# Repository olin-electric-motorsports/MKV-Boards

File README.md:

# MKV-Boards
Repository for all OEM MKV PCB Projects

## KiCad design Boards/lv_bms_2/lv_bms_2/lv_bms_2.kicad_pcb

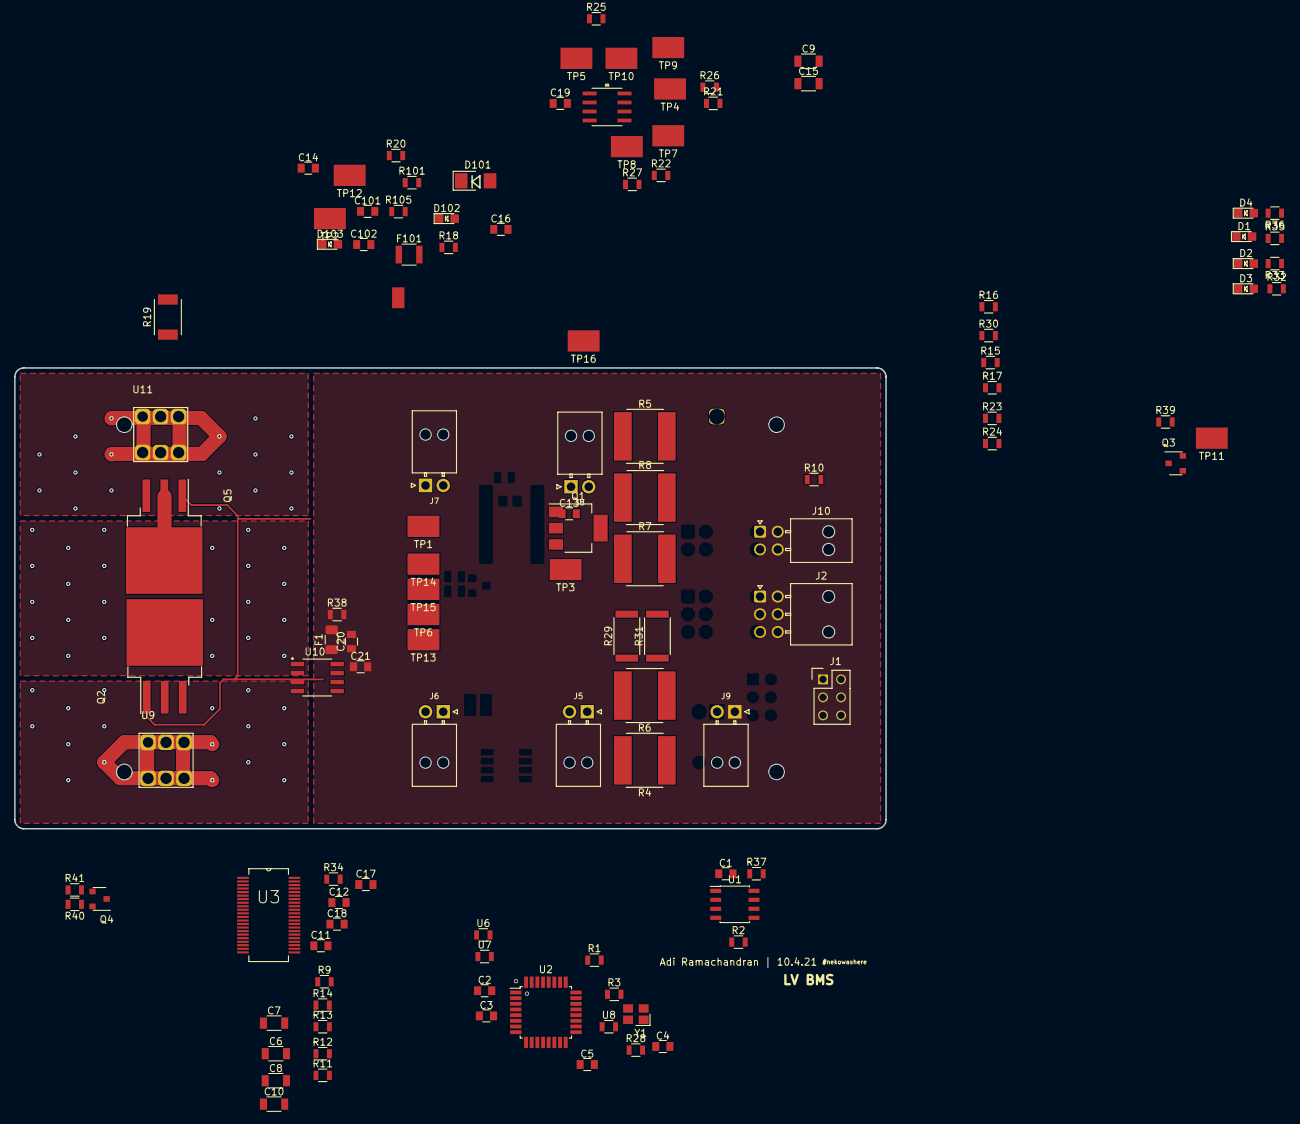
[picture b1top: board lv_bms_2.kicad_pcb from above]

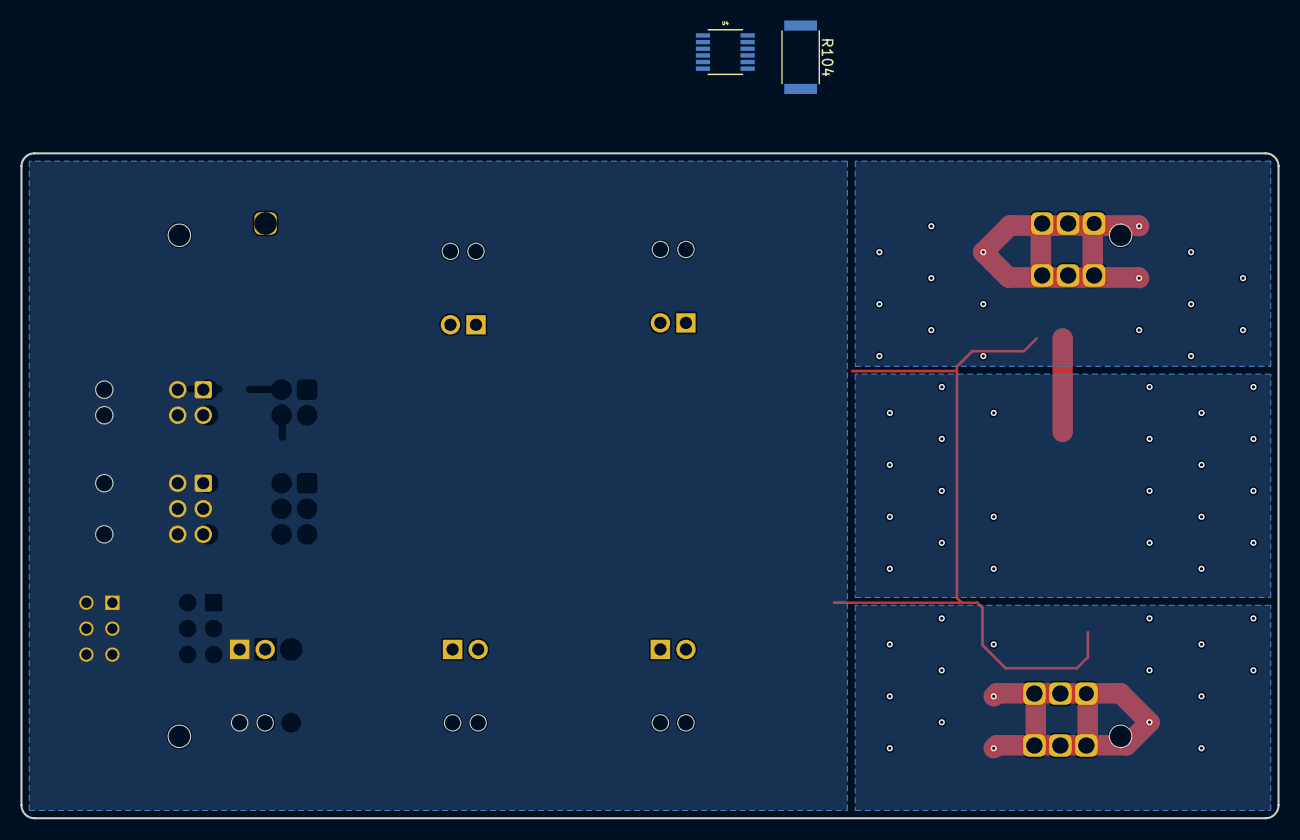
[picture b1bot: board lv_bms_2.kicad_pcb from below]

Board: 4 copper layers, 122.9 x 65.0 mm, 117 parts (2 on the bottom side), 76 nets.

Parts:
C1, C2, C13, C18, C19, C101: C_0.1uF; C_0805_OEM
C3: C_100pF; C_0805_OEM
C4, C5: C_30pF; C_0805_OEM
C6, C7, C8, C9, C10, C15: C_10nF; C_1206_OEM
C11, C12, C17, C21: C_1uF; C_0805_OEM
C14: C_470pF; C_0805_OEM
C16: C_10uF; C_0805_OEM
C20: C_1nf; C_0805_OEM
C102: C_2.2uF; C_0805_OEM
D1, D2: LED_0805_Red; LED_0805_OEM
D3, D4, D102, D103: LED_0805; LED_0805_OEM
D101: D_Zener_18V; DO-214AA
F1: 0685P9500-01; Fuse_1206
F101: F_500mA_16V; Fuse_1210
J1: CONN_02X03; Pin_Header_Straight_2x03
J2: NanoFit_RA_TH_06; NanoFit_RA_6
J5, J6, J7, J8, J9: NanoFit_RA_TH_02; NanoFit_Molex_1x02x2.50mm_Angled_OEM
J10: NanoFit_RA_TH_04; NanoFit_RA_4
Q1: NSS1C201MZ4; SOT-223
Q2, Q5: SQM110P06; TO-263-3-TabPin2
Q3, Q4: MMBF170; SOT-23-3_OEM
R1, R9, R10, R11, R12, R13, R14: R_100; R_0805_OEM
R2: R_120_DNP; R_0805_OEM
R3, R15, R16, R17, R20, R23, R24, R28, R30, R34, R40: R_10K; R_0805_OEM
R4, R5, R6, R7, R8: R_30_6W_1%; 356030RFT
R18, R21, R26, R37, R38, R39: R_100K; R_0805_OEM
R19: R_1.5k; R_2010_Vishay
R22, R27: R_1M; R_0805_OEM
R25: R_402K; R_0805_OEM
R29, R31, R104: R_0_2512; R_2512_OEM
R32, R33, R35, R36, R105: R_200; R_0805_OEM
R41: R_10; R_0805_OEM
R101: R_1K; R_0805_OEM
TP1, TP2, TP3, TP4, TP5, TP6, TP7, TP8, TP9, TP10, TP11, TP12, TP13, TP14, TP15, TP16: Test_Point_SMD
U1: MCP2561-E_SN; SOIC-8_3.9x4.9mm_Pitch1.27mm_OEM
U2: ATMEGA16M1; TQFP-32_7x7mm_Pitch0.8mm
U3: LTC6810HG-2; SOP50P780X200-44N
U4: LT3066IMSE-5; MSOP-12_MSE
U5: LT1017IS8; SO-8_S
U6, U7, U8: R_500; R_0805_OEM
U9, U11: redcube-7461057; redcube_pressfit_6pin
U10: ACHS-7124; OPTO_HCPL-070A-000E
Y1: Crystal_SMD; Crystal_SMD_FA238

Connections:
+5V: C1.1, C2.1, C19.1, C21.1, J1.2, R1.1, R3.1, R15.1, R16.1, R17.1, R23.1, R24.1, R28.1, R30.1, R34.1, R37.1, R104.2, U1.3, U2.4, U5.6, U10.8
/BATTERY_SIDE_DIV_SIG: R21.2, R22.1, TP7.1
/BATT_1: J2.2, R7.2, R12.2
/BATT_2: J2.3, R6.2, R11.2
/BATT_3: J2.4, R5.2, R10.2
/BATT_4: F101.2, J2.5, R4.2, R9.2, R29.2, R31.2, TP12.1, U5.3
/CAN+: J10.4, R2.1, U1.7
/CAN-: J10.3, R2.2, U1.6
/CAN_RX: U1.4, U2.7
/CAN_STBY: R37.2, U1.8, U2.23
/CAN_TX: U1.1, U2.6
/COMP_1_OUT: TP4.1, U2.16, U5.7
/COMP_2_OUT: TP10.1, U2.26, U5.5
/CSB: R28.2, U2.15, U3.36
/CURRENT_SENSE_SIGNAL: U2.28, U10.7
/LED_0_+: R32.1, U2.8
/LED_1_+: R33.1, U2.9
/LED_2_+: R35.1, U2.24
/LOAD_SIDE_CURRENT_PATH: Q5.3, R25.1, R26.1, TP9.1, U11.1
/LOAD_SIDE_DIV_SIG: R26.2, R27.1, TP8.1, U5.4
/LOAD_SWITCH_FET_DRIVE: Q4.1, R38.1, U2.25
/MISO: J1.1, U2.1, U6.1
/MISO_LIM: R34.2, U3.40, U6.2
/MOSI: J1.4, U2.2, U7.1
/MOSI_LIM: U3.41, U7.2
/ON_STATE_CMPNTS_-: C20.2, C21.2, J5.2, J6.2, J7.1, J8.1, J9.1, Q3.3, TP11.1, TP15.1, U10.5
/ON_STATE_CMPNTS_FET_DRIVE: Q3.1, R36.1, R39.1, U2.30
/PACK_SIDE_CURRENT_PATH: F1.2, R21.1, R25.2, TP5.1, U10.1, U10.2
/RESET: J1.5, R3.2, U2.31
/SCK: J1.3, U2.12, U8.1
/SCK_LIM: U3.37, U8.2
/THERM_0_+: J7.2, R30.2, U2.27
/THERM_1_+: J8.2, R24.2, U2.17
/THERM_2_+: J9.2, R23.2, U2.18
/THERM_3_+: J6.1, R17.2, U2.22
/THERM_4_+: J5.1, R16.2, U2.13
/THERM_5_+: R15.2, TP14.1, U2.14
/VREG: C17.1, Q1.3, TP3.1, U3.32
GND: C1.2, C2.2, C3.2, C4.2, C5.2, C11.2, C12.2, C13.2, C14.2, C15.2, C16.2, C17.2, C18.1, C19.2, C101.2, C102.2, D1.1, D2.1, D3.1, D4.1, D101.2, D102.1, D103.1, J1.6, J2.1, J10.1, J10.2, Q3.2, Q4.2, R8.2, R13.2, R20.2, R22.2, R27.2, R38.2, R39.2, TP16.1, U1.2, U2.5, U2.20, U3.1, U3.21, U3.22, U3.23, U3.24, U3.26, U3.27, U3.28, U3.29, U3.34, U3.35, U3.38, U3.39, U3.43, U3.44, U4.6, U4.8, U5.2, Y1.2, Y1.4
unnamed: C3.1, R1.2, U2.19
unnamed: C4.1, U2.11, Y1.1
unnamed: C5.1, U2.10, Y1.3
unnamed: C6.1, R9.1, TP1.1, U3.6, U3.8
unnamed: C6.2, C7.1, R10.1, U3.10
unnamed: C7.2, C8.1, R11.1, U3.12
unnamed: C8.2, C9.1, R12.1, U3.14
unnamed: C9.2, C10.1, R13.1, U3.16
unnamed: C10.2, R8.1, U3.17
unnamed: C11.1, U3.30
unnamed: C12.1, U3.31
unnamed: C13.1, Q1.2, Q1.4, R14.2
unnamed: C14.1, U4.1
unnamed: C15.1, U4.7
unnamed: C16.1, R104.1, R105.1, TP2.1, U4.10, U4.11, U4.12
unnamed: C18.2, R29.1, U3.3
unnamed: C20.1, U10.6
unnamed: C101.1, C102.1, D101.1, F101.1, R18.1, R101.1, U4.2, U4.3
unnamed: D1.2, R32.2
unnamed: D2.2, R33.2
unnamed: D3.2, R35.2
unnamed: D4.2, R36.2
unnamed: D102.2, R101.2
unnamed: D103.2, R105.2
unnamed: F1.1, U9.1
unnamed: Q1.1, U3.33
unnamed: Q2.1, Q5.1, R40.2, R41.1, TP13.1
unnamed: Q2.2, Q5.2, R40.1, TP6.1
unnamed: Q2.3, U10.3, U10.4
unnamed: Q4.3, R41.2
unnamed: R4.1, U3.9
unnamed: R5.1, U3.11
unnamed: R6.1, U3.13
unnamed: R7.1, U3.15
unnamed: R14.1, R31.1
unnamed: R18.2, R19.1, U4.4
unnamed: R19.2, R20.1

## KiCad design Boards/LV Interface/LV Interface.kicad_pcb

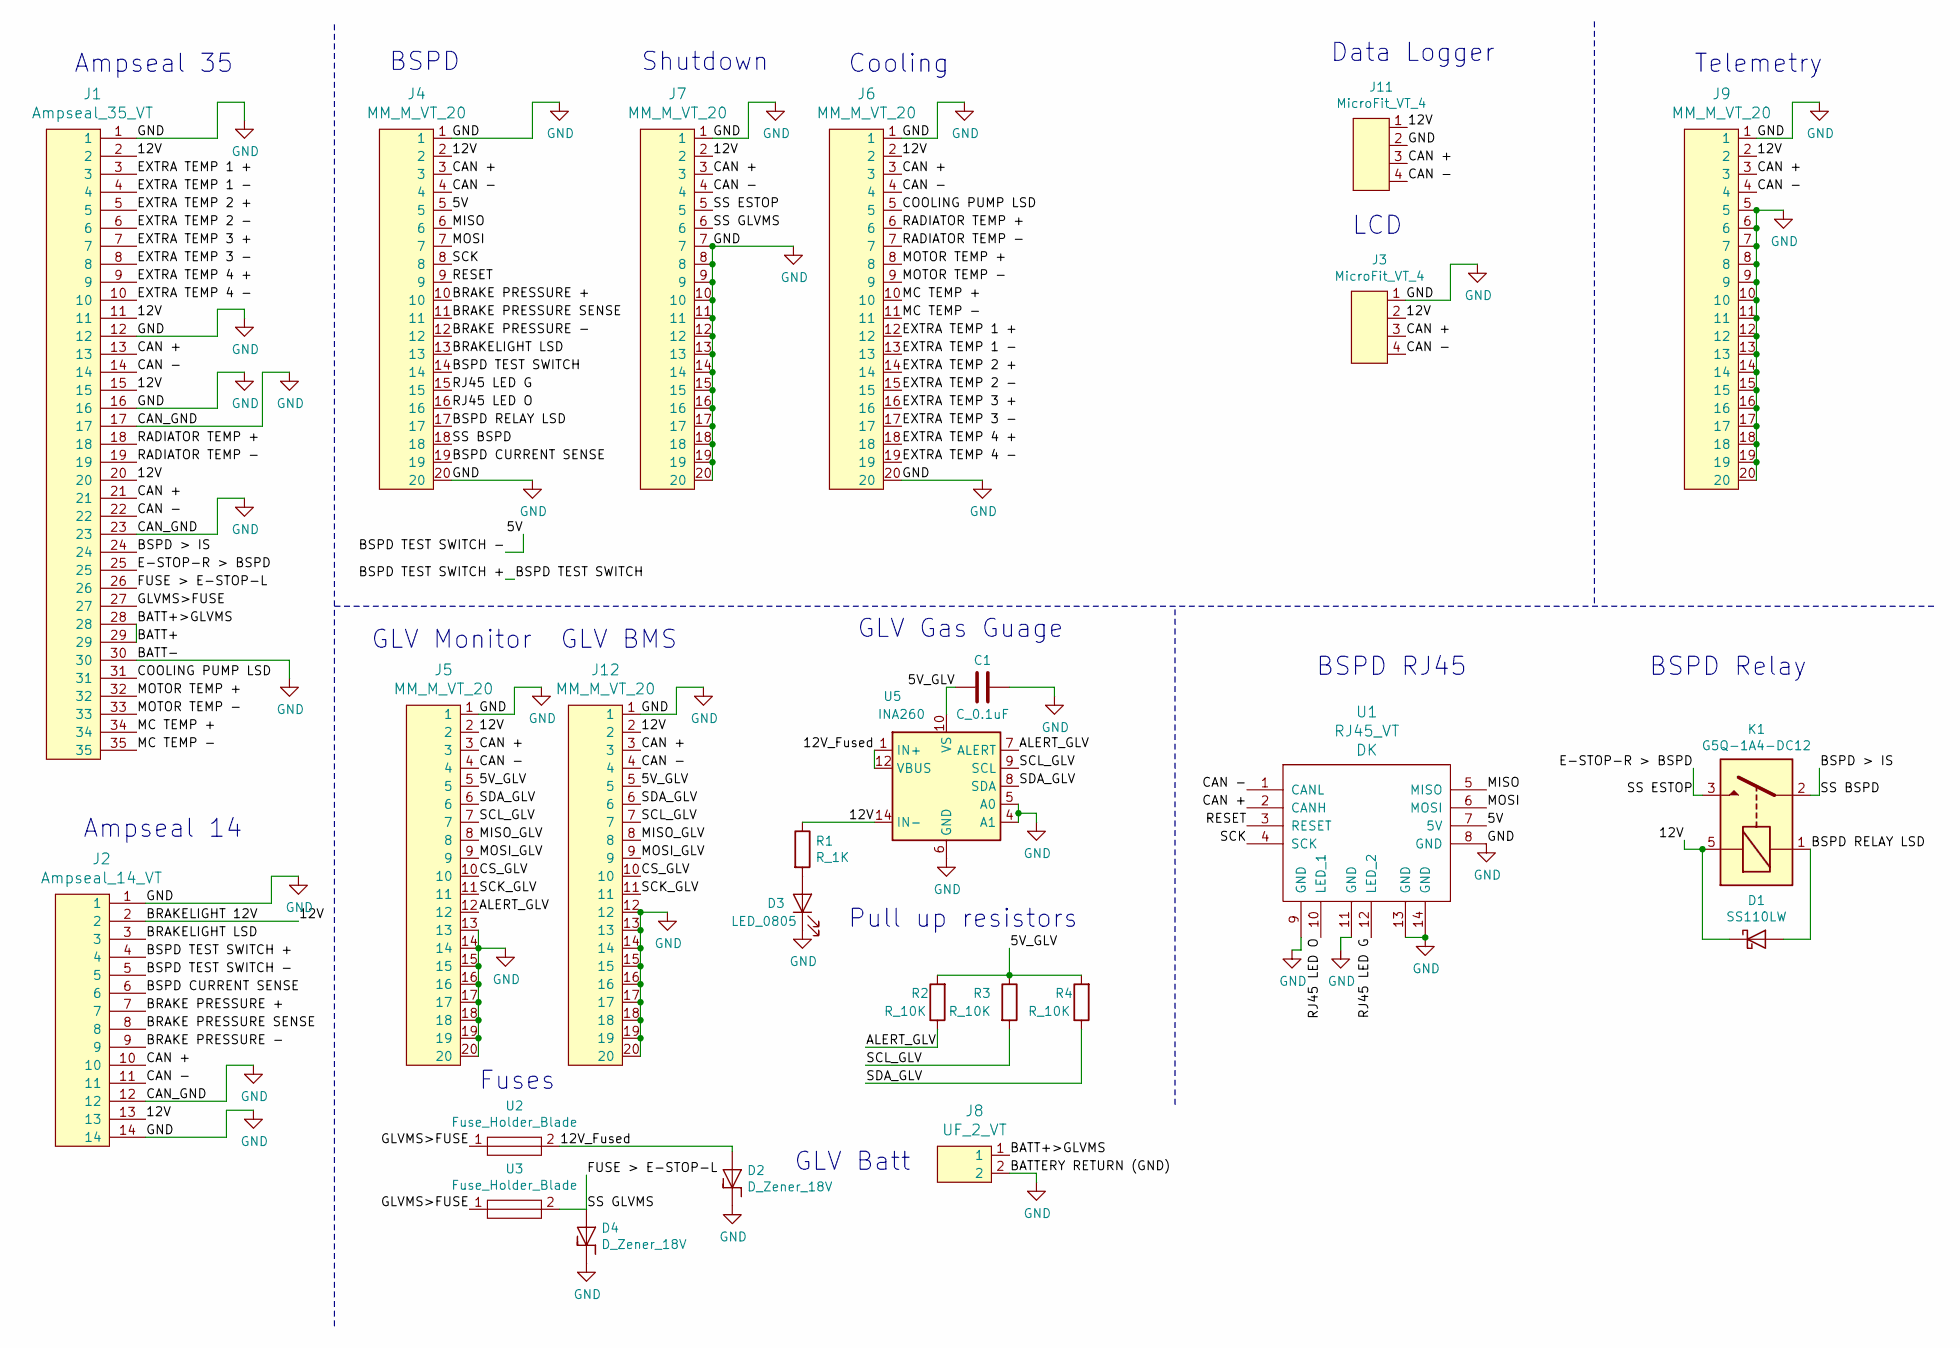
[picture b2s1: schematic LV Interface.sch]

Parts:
C1: C_0.1uF; C_0805_OEM; MPN 478-3352-1-ND
D1: SS110LW; D_SOD-123W_OEM; MPN SS110LWRVGCT-ND
D2, D4: D_Zener_18V; DO-214AA; MPN SMBJ5355B-TPMSCT-ND
D3: LED_0805; LED_0805_OEM; MPN 475-1410-1-ND
J1: Ampseal_35_VT; Ampseal_35; MPN 1-776231-1
J2: Ampseal_14_VT; Ampseal_14; MPN 1-776261-1
J3, J11: MicroFit_VT_4
J4, J5, J6, J7, J9, J12: MM_M_VT_20; micromatch_female_ra_20; MPN 2-215464-0
J8: UF_2_VT; Ultrafit_2; MPN WM11570-ND
K1: G5Q-1A4-DC12; Relay_SPST_OMRON-G5Q-1A4_OEM
R1: R_1K; R_0805_OEM; MPN RNCP0805FTD1K00CT-ND
R2, R3, R4: R_10K; R_0805_OEM; MPN CRS0805-FX-1002ELFCT-ND
U1: RJ45_VT; RJ45-Vertical; MPN MRJ-5481-01-ND
U2, U3: Fuse_Holder_Blade; Fuse_Block_Holder
U5: INA260; TSSOP-16_4.4x5mm_P0.65mm

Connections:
/5V: J2.5, J4.5, U1.7 (5V)
/5V_GLV: C1.2, J5.5, J12.5, R2.2, R3.1, R4.2, U5.10 (VS)
/12V: D1.1 (K), J1.2, J1.11, J1.15, J1.20, J2.2, J2.13, J3.2, J4.2, J5.2, J6.2, J7.2, J9.2, J11.1, J12.2, K1.5, R1.1, U5.14 (IN-), U5.15 (IN-), U5.16 (IN-); also elsewhere on the board
/12V_Fused: D2.2 (A), U2.2, U5.1 (IN+), U5.2 (IN+), U5.3 (IN+), U5.12 (VBUS)
/ALERT_GLV: J5.12, R2.1, U5.7 (ALERT)
/BATT+: J1.28, J1.29, J8.1
/BRAKE PRESSURE +: J2.7, J4.10
/BRAKE PRESSURE -: J2.9, J4.12
/BRAKE PRESSURE SENSE: J2.8, J4.11
/BRAKELIGHT LSD: J2.3, J4.13
/BSPD > IS: J1.24, J4.18, K1.2
/BSPD CURRENT SENSE: J2.6, J4.19
/BSPD RELAY LSD: D1.2 (A), J4.17, K1.1
/BSPD TEST SWITCH: J2.4, J4.14
/CAN +: J1.13, J1.21, J2.10, J3.3, J4.3, J5.3, J6.3, J7.3, J9.3, J11.3, J12.3, U1.2 (CANH); also elsewhere on the board
/CAN -: J1.14, J1.22, J2.11, J3.4, J4.4, J5.4, J6.4, J7.4, J9.4, J11.4, J12.4, U1.1 (CANL); also elsewhere on the board
/COOLING PUMP LSD: J1.31, J6.5
/CS_GLV: J5.10, J12.10
/E-STOP-R > BSPD: J1.25, J7.5, K1.3
/EXTRA TEMP 1 +: J1.3, J6.12
/EXTRA TEMP 1 -: J1.4, J6.13
/EXTRA TEMP 2 +: J1.5, J6.14
/EXTRA TEMP 2 -: J1.6, J6.15
/EXTRA TEMP 3 +: J1.7, J6.16
/EXTRA TEMP 3 -: J1.8, J6.17
/EXTRA TEMP 4 +: J1.9, J6.18
/EXTRA TEMP 4 -: J1.10, J6.19
/FUSE > E-STOP-L: D4.2 (A), J1.26, J7.6, U3.2
/GLVMS>FUSE: J1.27, U2.1, U3.1
/MC TEMP +: J1.34, J6.10
/MC TEMP -: J1.35, J6.11
/MISO: J4.6, U1.5 (MISO)
/MISO_GLV: J5.8, J12.8
/MOSI: J4.7, U1.6 (MOSI)
/MOSI_GLV: J5.9, J12.9
/MOTOR TEMP +: J1.32, J6.8
/MOTOR TEMP -: J1.33, J6.9
/RADIATOR TEMP +: J1.18, J6.6
/RADIATOR TEMP -: J1.19, J6.7
/RESET: J4.9, U1.3 (RESET)
/RJ45 LED G: J4.15, U1.12 (LED_2)
/RJ45 LED O: J4.16, U1.10 (LED_1)
/SCK: J4.8, U1.4 (SCK)
/SCK_GLV: J5.11, J12.11
/SCL_GLV: J5.7, J12.7, R3.2, U5.9 (SCL)
/SDA_GLV: J5.6, J12.6, R4.1, U5.8 (SDA)
GND: C1.1, D2.1 (K), D3.1 (K), D4.1 (K), J1.1, J1.12, J1.16, J1.17, J1.23, J1.30, J2.1, J2.12, J2.14, J3.1, J4.1, J4.20, J5.1, J5.13, J5.14, J5.15, J5.16, J5.17, J5.18, J5.19, J5.20, J6.1, J6.20, J7.1, J7.7, J7.8, J7.9, J7.10, J7.11, J7.12, J7.13, J7.14, J7.15, J7.16, J7.17, J7.18, J7.19, J7.20, J8.2, J9.1, J9.5, J9.6, J9.7, J9.8, J9.9, J9.10, J9.11, J9.12, J9.13, J9.14, J9.15, J9.16, J9.17, J9.18, J9.19, J9.20, J11.2, J12.1, J12.12, J12.13, J12.14, J12.15, J12.16, J12.17, J12.18, J12.19, J12.20, U1.8 (GND), U1.9 (GND), U1.11 (GND), U1.13 (GND), U1.14 (GND), U5.4 (A1), U5.5 (A0), U5.6 (GND), U5.11 (GND); also elsewhere on the board
unnamed: D3.2 (A), R1.2

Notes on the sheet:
Ampseal 35
Ampseal 14
BSPD
Shutdown
Cooling
Telemetry
LCD
GLV Monitor
GLV BMS
BSPD Relay
Fuses
BSPD RJ45
Data Logger
GLV Gas Guage
GLV Batt
Pull up resistors

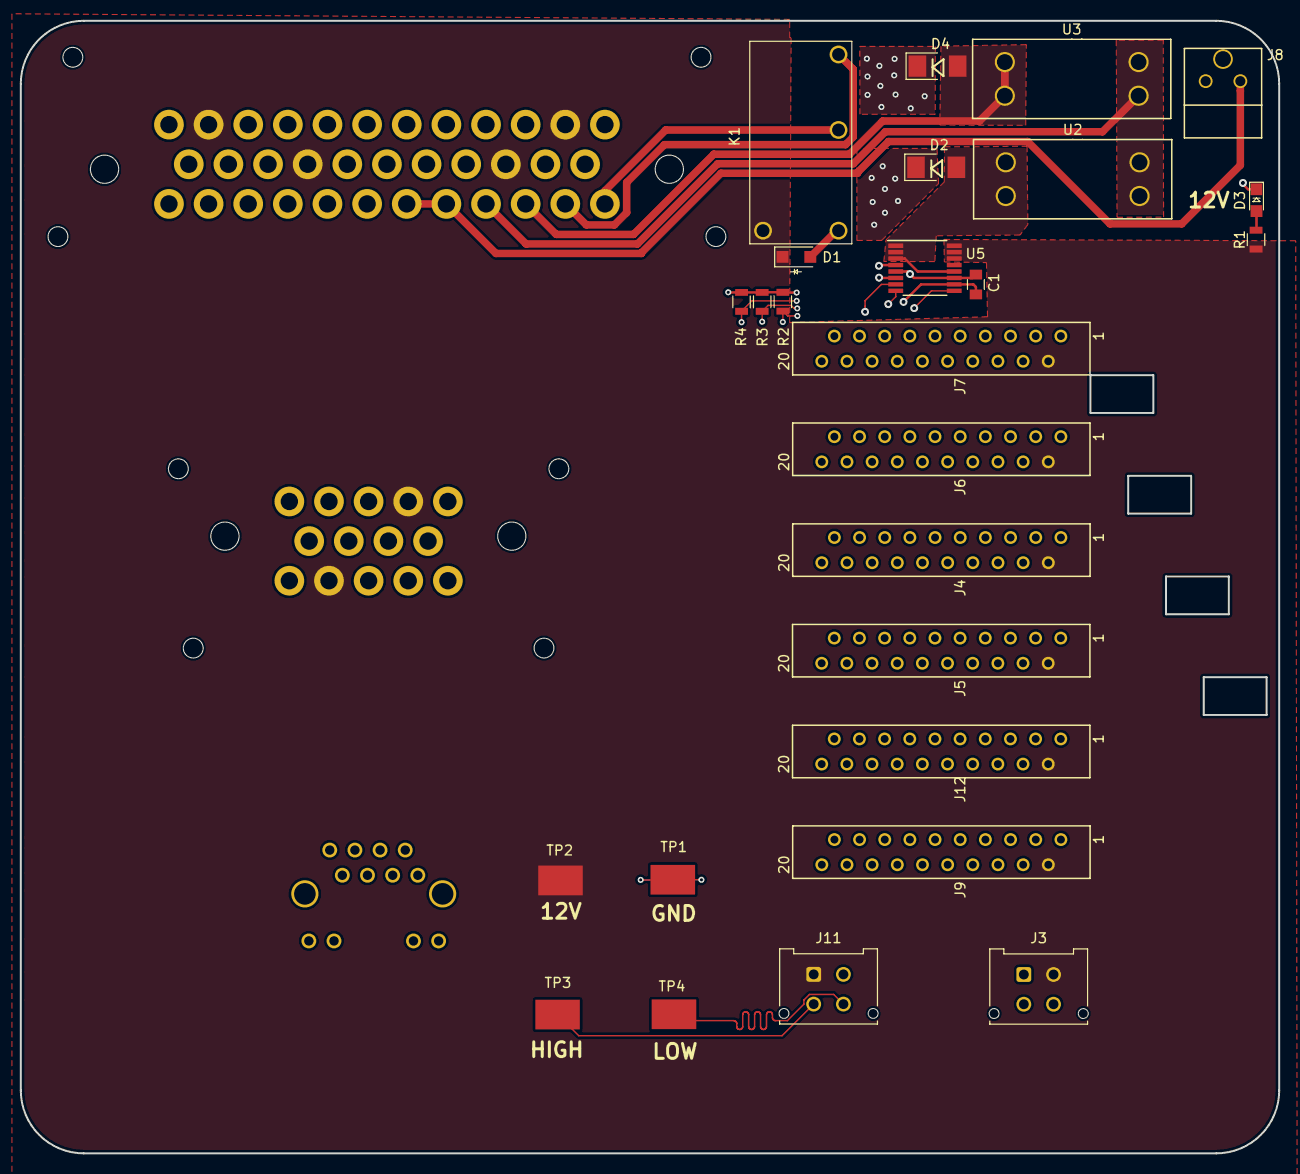
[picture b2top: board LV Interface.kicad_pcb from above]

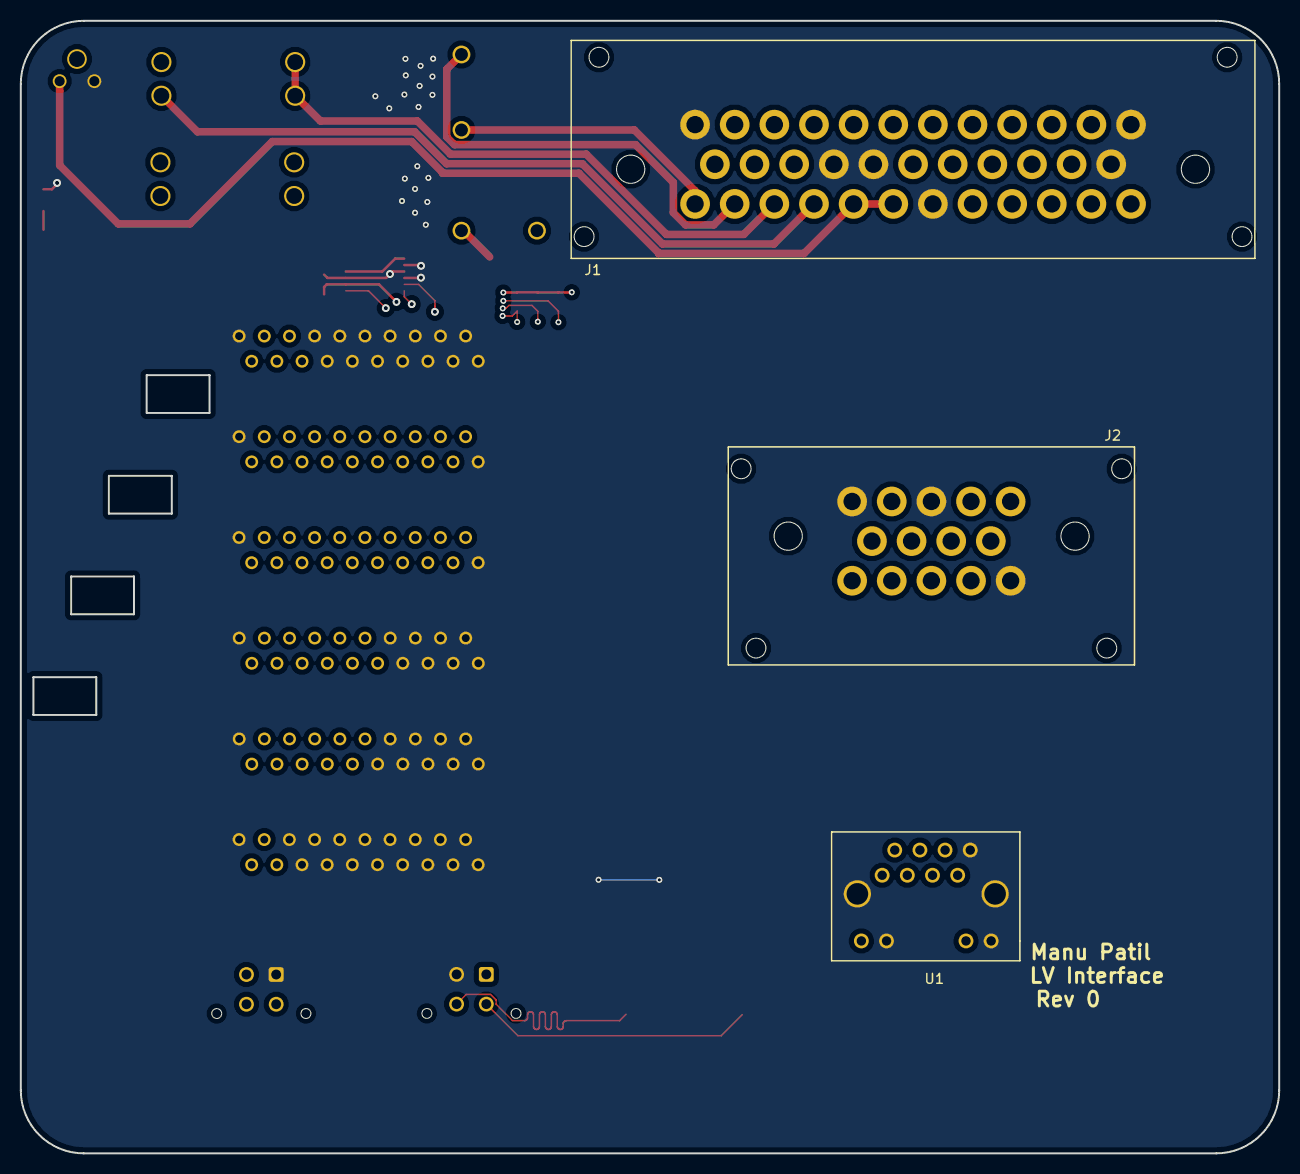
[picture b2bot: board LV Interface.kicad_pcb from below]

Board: 4 copper layers, 127.0 x 114.3 mm, 29 parts (3 on the bottom side), 48 nets.

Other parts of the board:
TP1, TP2, TP3, TP4: Test_Point_SMD

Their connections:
/12V: TP2.1; also elsewhere on the board
/CAN +: TP3.1; also elsewhere on the board
/CAN -: TP4.1; also elsewhere on the board
GND: TP1.1; also elsewhere on the board

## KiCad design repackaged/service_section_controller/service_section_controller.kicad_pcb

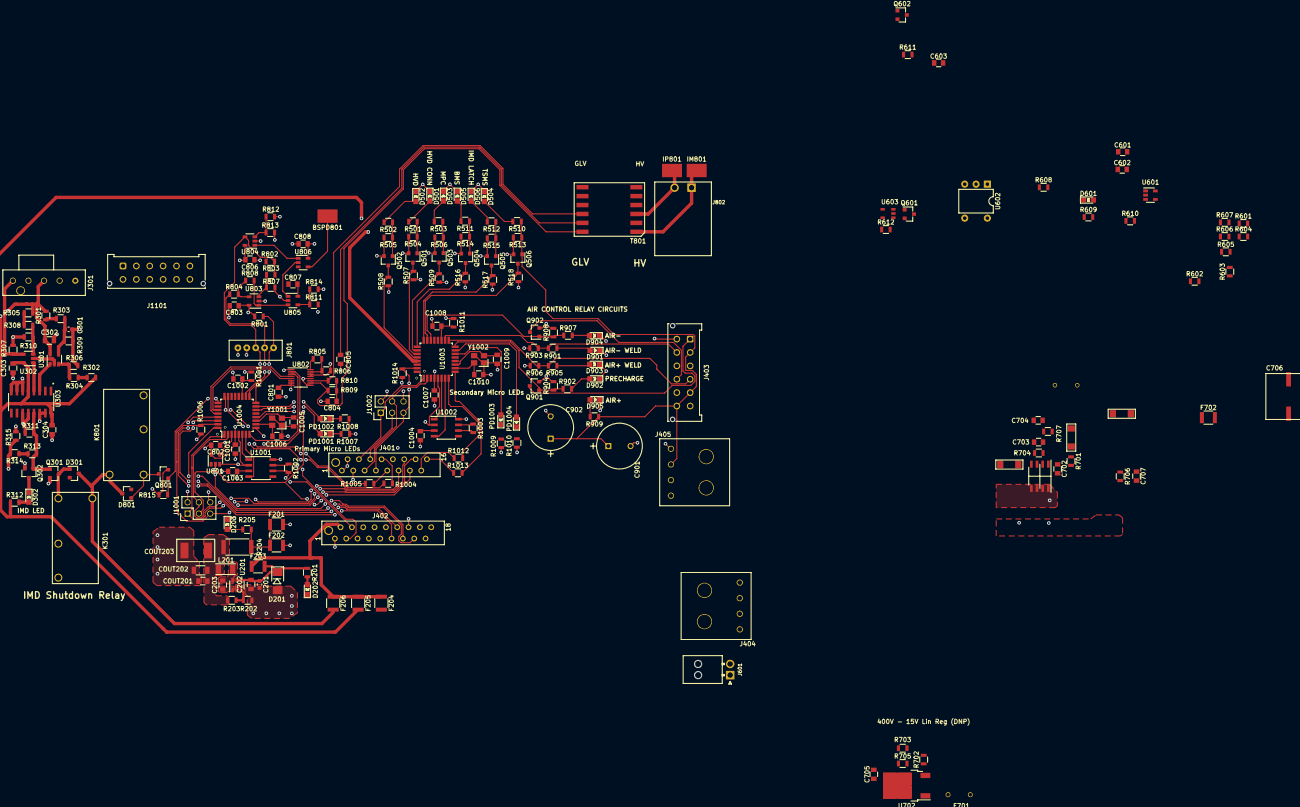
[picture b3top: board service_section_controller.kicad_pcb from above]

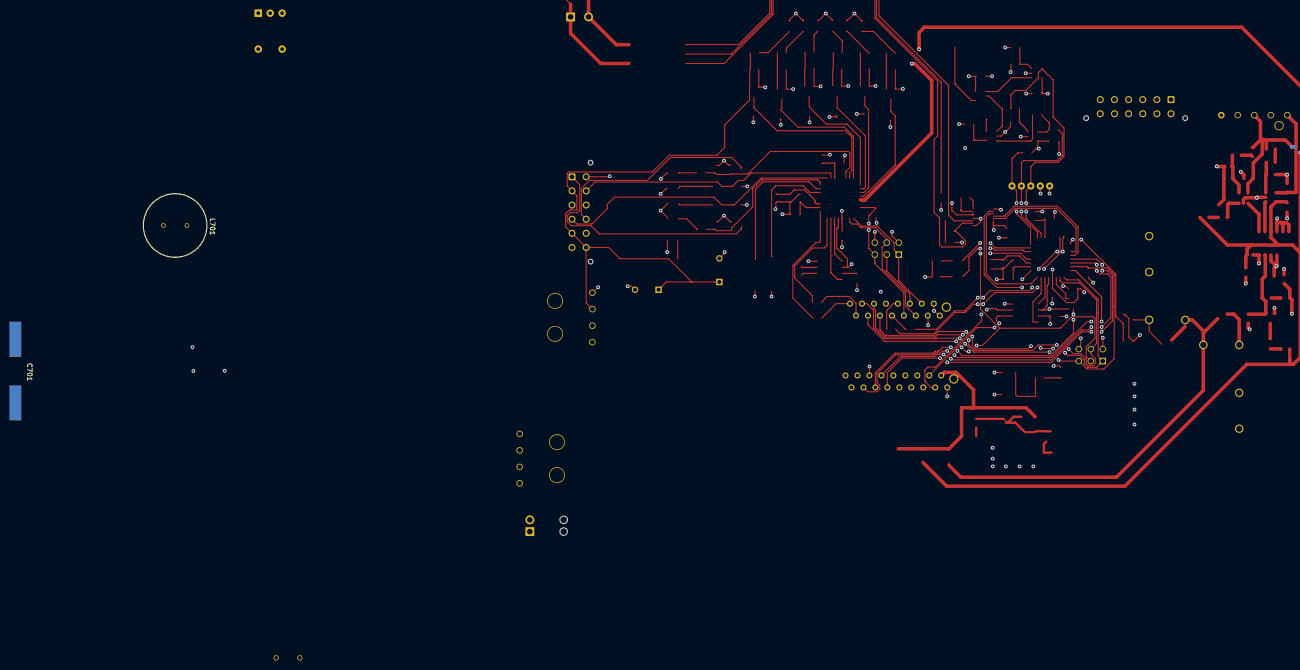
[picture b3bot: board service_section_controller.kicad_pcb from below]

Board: 4 copper layers, 222 parts (2 on the bottom side), 149 nets.

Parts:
BSPD801: Test_Point_SMD
C201, C301: C_2.2uF; C_0603_1608Metric
C202, C203, C302, C303, C304, C602, C801, C802, C803, C806, C807, C808, C1001, C1003, C1004, C1007: C_0.1uF; C_0805_OEM
C601: C_10uF; C_0805_OEM
C603, C705, C707: C_1uF; C_0805_OEM
C701: C_10uF_450V
C702: C_2.2uF; C_0805_OEM
C703: C_470pF; C_0805_OEM
C704: C_.22uF; C_0805_OEM
C706: C_100uF+
C804, C805: C_10nF; C_0805_OEM
C901, C902: CP_1mF; C_Radial_D10_L13_P5_OEM
C1002, C1008: C_100pF; C_0805_OEM
C1005, C1006, C1009, C1010: C_30pF; C_0805_OEM
COUT201: C_47uF; C_0805_OEM
COUT202: C_22uF; C_1206_OEM
COUT203: C_33uF; Fuse_1812
D201: D_Zener_18V; DO-214AA
D202, D203, D302, D501, D502, D503, D504, D505, D506, D601, D901, D902, D903, D904, D905: LED_0805; LED_0805_OEM
D301, D801: BAS40-00; SOT-23
D701, D702, D703: Diode_600V_1A_SM
F201, F202, F203, F204, F205, F206, F702: 500mA; Fuse_1210
F701: F_21mA_420V
IM801: Test_Point_SMD
IP801: Test_Point_SMD
J301: UF_5_VT; Ultrafit_5
J401: MM_F_VT_16; micromatch_female_vert_16
J402: MM_F_VT_18; micromatch_female_vert_18
J403, J1101: MicroFit_VT_12
J404, J405: Ultrafit_4_RA
J601: NanoFit_2; NanoFit_Molex_1x02x2.50mm_Angled_OEM
J801: B5B-PH-K-S
J802: isoSPI-Cutout; iso_spi_cutout
J1001, J1002: CONN_02X03; Pin_Header_Straight_2x03
K301, K801: G5Q-1A4-DC12; Relay_SPST_OMRON-G5Q-1A4_OEM
L201: L_100uH; L_100uH_OEM
L701: L_1.2mH
PD1001, PD1002, PD1003, PD1004: LED_0805; LED_0805_OEM
Q301, Q302, Q501, Q502, Q503, Q504, Q505, Q506, Q601, Q602, Q801, Q901, Q902: SSM3K333R; SOT-23F
R201, R301, R312, R314, R501, R502, R503, R510, R511, R512, R609, R805, R806, R813, R909: R_1K; R_0805_OEM
R202: R_25K; R_0805_OEM
R203, R504, R505, R506, R513, R514, R515: R_100K; R_0805_OEM
R204: R_0_2512; R_2512_OEM
R205, R901, R902, R905, R907, R1002, R1003, R1004, R1005, R1007, R1008, R1009, R1010, R1012, R1013: R_200; R_0805_OEM
R302, R305, R307, R313: R_2.2K; R_0805_OEM
R303: R_120K; R_0805_OEM
R304, R308: R_300K; R_0805_OEM
R306, R310, R311: R_604K; R_0805_OEM
R309: R_1.82M; R_0805_OEM
R315: R_1.13K; R_0805_OEM
R507, R508, R509, R516, R517, R518, R605, R611, R612, R701, R801, R802, R803, R804, R807, R808, R812, R814, R815, R903, R904, R906, R908, R1006, R1014: R_10K; R_0805_OEM
R601, R604, R606, R607: R_270K; R_0805_OEM
R602: R_1.91K; R_0805_OEM
R603: R_51.1K; R_0805_OEM
R608: R_1.43K; R_0805_OEM
R610: R_499; R_0805_OEM
R702: R_43k; R_0805_OEM
R703, R707: R_23.7K; R_0805_OEM
R704: R_4.99K; R_0805_OEM
R705: R_6.04K; R_0805_OEM
R706: R_3K; R_0805_OEM
R809, R810: R_60.4; R_0805_OEM
R811: R_475; R_0805_OEM
R1001, R1011: R_100; R_0805_OEM
T801: T_LAN_SM91501ALE
U201: TPS560430YF; SOT-23-6_OEM
U301, U302: TLV3701QDBVRG4Q1; SOT-23-5_OEM
U303: CD4044BDR; SOIC127P600X175-16N
U601: MCP6001; SOT-23-5
U602: CPC1025NTR; DIP-5-6_W7.62mm
U603: BU4S11G2-TR; SSOP5
U701: MP9488; Converter_DCDC_MPS_MP9488
U702: LR8K4-G; TO-252-2
U801: SN74LVC1G17; SOT-23-5
U802: LTC6820HMS; MSOP-16_3x4mm_P0.5mm
U803, U804, U805: MCP6001; SOT-23-5_OEM
U806: SN74LVC1G32DBVR; SOT-23-5_OEM
U1001, U1002: MCP2561-E_SN; SOIC-8_3.9x4.9mm_Pitch1.27mm_OEM
U1003: ATMEGA16M1; TQFP-32_7x7mm_Pitch0.8mm
U1004: ATMEGA64M1; TQFP-32_7x7mm_Pitch0.8mm
Y1001, Y1002: Crystal_SMD; Crystal_SMD_FA238

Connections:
5V_BMS: C801.1, C802.2, C803.1, C806.1, C807.1, C808.1, C1001.1, C1003.1, F201.2, J401.3, J801.1, J1001.2, R801.1, R802.2, R811.2, R812.1, R1001.1, R1006.1, U801.5, U802.6, U802.7, U802.8, U802.9, U802.12, U803.5, U804.5, U805.5, U806.5, U1001.3, U1004.4
12V_IMD: C302.2, C303.2, C304.2, F205.2, J301.3, R301.2, R302.2, R305.2, R312.1, U301.5, U302.5, U303.5, U303.16
12V_SHUTDOWN: D301.3, D801.3, F206.2, K301.5, K801.5
12V_TSAL: C603.2, F204.2, J402.5, J402.6, J402.7, U602.4, U603.2, U603.5
15V+: C601.2, C602.2, C705.1, F702.2, R602.2, R705.1, U601.5, U702.2
15V-: C601.1, C602.1, C701.1, C705.2, C706.2, C707.2, D702.1, J404.2, J404.4, J601.1, R603.2, R605.2, R609.2, R703.2, R706.2, U601.2, U602.2
+5V: F201.1, F202.1, R204.1
+AIR_AUX+: C1004.1, C1007.1, F202.2, J401.10, J403.3, J403.7, J1002.2, R507.1, R508.1, R509.1, R516.1, R517.1, R518.1, R1011.1, R1014.1, U1002.3, U1003.4
+AIR_AUX-: J403.4, R905.1, R906.1, U1003.17
+AIR_COIL+: C901.1, C902.1, J403.2, J403.5, J403.9, J403.12, J405.2, J1101.8, J1101.12, Q506.1, R510.1, R513.1, R909.1
+AIR_COIL-: C201.2, C202.2, C301.2, C302.1, C303.1, C304.1, C603.1, C801.2, C802.1, C803.2, C804.2, C805.2, C806.2, C807.2, C808.2, C901.2, C902.2, C1001.2, C1002.2, C1003.2, C1004.2, C1005.2, C1006.2, C1007.2, C1008.2, C1009.2, C1010.2, COUT201.2, COUT202.2, COUT203.2, D201.2, D202.1, D203.1, D501.1, D502.1, D503.1, D504.1, D505.1, D506.1, D901.1, D902.1, D903.1, D904.1, D905.1, J301.2, J301.4, J301.5, J401.1, J401.2, J402.1, J402.14, J403.6, J403.11, J405.1, J801.2, J1001.6, J1002.6, Q301.2, Q302.2, Q501.2, Q502.2, Q503.2, Q504.2, Q505.2, Q506.2, Q601.2, Q602.2, Q801.2, Q901.2, Q902.2, R202.2, R306.1, R307.2, R309.2, R310.1, R311.2, R315.2, R504.2, R505.2, R506.2, R513.2, R514.2, R515.2, R611.2, R612.2, R806.2, R807.1, R813.2, R814.1, R815.1, R903.2, R904.2, R906.2, R908.2, R1007.2, R1008.2, R1009.2, R1010.2, U201.2, U301.2, U302.2, U303.6, U303.7, U303.8, U303.11, U303.12, U303.14, U303.15, U603.3, U801.3, U802.1, U802.13, U802.14, U803.2, U804.2, U805.2, U806.3, U1001.2, U1001.8, U1002.2, U1002.8, U1003.5, U1003.20, U1004.5, U1004.20, Y1001.2, Y1001.4, Y1002.2, Y1002.4
+BATT: F203.1, F204.1, F205.1, F206.1, J402.2
-AIR_AUX-: J403.8, R901.1, R903.1, U1003.18
-AIR_COIL-: J403.10, Q902.3
-AIR_LSD: Q902.1, R907.1, R908.1, U1003.22
/imd_latch/LATCH_OUTPUT: Q301.1, Q302.1, R311.1, R313.1, U303.13
/micros/PM_DBG_1: PD1001.2, U1004.14
/micros/PM_DBG_2: PD1002.2, U1004.15
/micros/PM_RXCAN: U1001.4, U1004.7
/micros/PM_TXCAN: U1001.1, U1004.6
/micros/SM_DBG_1: PD1003.2, U1003.14
/micros/SM_DBG_2: PD1004.2, U1003.15
/micros/SM_RXCAN: U1002.4, U1003.7
/micros/SM_TXCAN: U1002.1, U1003.6
/power_main/12v_BUCK: C201.1, C202.1, D201.1, F203.2, R201.1, U201.4, U201.5
/power_secondary.sch/FB: C703.1, R704.1, R707.2, U701.2
/power_secondary.sch/SW: C702.2, C703.2, C704.2, D702.2, L701.1, R704.2, U701.3, U701.4
/power_secondary.sch/VCC: C702.1, R701.2, U701.1
/tsal_ail/TSAL_FLAG: Q601.1, R611.1, U602.3, U603.1
AIL+: J601.2, R608.2
BMS_RELAY_DRIVE: Q801.1, R815.2, U1004.25
BSPD_CURRENT_SENSE: BSPD801.1, J402.15, U806.4, U1004.32
CANH: J402.3, R1002.1, R1003.1, U1001.7, U1002.7
CANL: J402.4, R1002.2, R1003.2, U1001.6, U1002.6
CHARGE_ENABLE1: J402.11, U1004.29
CHARGE_ENABLE2: J402.12, U1004.30
CS_ISO: U802.5, U1004.27
DETECT_BMS: J1101.5, J1101.11, K301.2, K801.2, Q504.1, R511.1, R514.1
DETECT_HVD: J1101.1, J1101.7, Q502.1, R502.1, R505.1
DETECT_HVD_CONN: J1101.3, J1101.9, Q501.1, R501.1, R504.1
DETECT_IMD_LATCH: J1101.2, J1101.6, K301.3, Q505.1, R512.1, R515.1
DETECT_MPC: J1101.4, J1101.10, K801.3, Q503.1, R503.1, R506.1
FAN_PWM: J402.13, U801.2
FAN_PWM_RAW: U801.4, U1004.3
IM: IM801.1, J802.1, T801.1
IMD_Output: J301.1, R307.1, U302.4
IMD_STATUS_OUTPUT: R314.2, R315.1, U1003.29
IP: IP801.1, J802.2, T801.3
MISO_ISO: U802.3, U1004.8
MOSI_ISO: U802.2, U1004.9
unnamed: C203.1, L201.1, U201.6
unnamed: C203.2, U201.1
unnamed: C301.1, R303.1, R309.1, U301.4
unnamed: C704.1, D701.1, D703.2, R707.1
unnamed: C706.1, C707.1, D703.1, F702.1, L701.2, R706.1
unnamed: C804.1, R809.2, R810.1
unnamed: C805.1, T801.11
unnamed: C1002.1, R1001.2, U1004.19
unnamed: C1005.1, U1004.11, Y1001.1
unnamed: C1006.1, U1004.10, Y1001.3
unnamed: C1008.1, R1011.2, U1003.19
unnamed: C1009.1, U1003.11, Y1002.1
unnamed: C1010.1, U1003.10, Y1002.3
unnamed: COUT201.1, COUT202.1, COUT203.1, L201.2, R203.2, R204.2, R205.1
unnamed: D202.2, R201.2
unnamed: D203.2, R205.2
unnamed: D301.1, K301.1, Q301.3
unnamed: D302.1, Q302.3
unnamed: D302.2, R312.2
unnamed: D501.2, R501.2
unnamed: D502.2, R502.2
unnamed: D503.2, R503.2
unnamed: D504.2, R510.2
unnamed: D505.2, R511.2
unnamed: D506.2, R512.2
unnamed: D601.1, R609.1
unnamed: D601.2, R608.1, R610.2, U601.1
unnamed: D701.2, R701.1
unnamed: D801.1, K801.1, Q801.3
unnamed: D901.2, R901.2
unnamed: D902.2, R902.2
unnamed: D903.2, R905.2
unnamed: D904.2, R907.2
unnamed: D905.2, R909.2
unnamed: F701.1, U702.1
unnamed: PD1001.1, R1007.1
unnamed: PD1002.1, R1008.1
unnamed: PD1003.1, R1009.1
unnamed: PD1004.1, R1010.1
unnamed: Q602.1, R612.1, U603.4
unnamed: R202.1, R203.1, U201.3
unnamed: R301.1, R303.2
unnamed: R302.1, R304.2
unnamed: R304.1, R306.2, U301.3
unnamed: R305.1, R308.2
unnamed: R308.1, R310.2, U302.3
unnamed: R313.2, R314.1
unnamed: R601.1, R604.2
unnamed: R602.1, R603.1, U601.4
unnamed: R604.1, R606.2
unnamed: R605.1, R607.1, U601.3
unnamed: R606.1, R607.2
unnamed: R610.1, U602.1
unnamed: R702.1, R705.2, U702.3
unnamed: R702.2, R703.1
unnamed: R803.2, R807.2, U803.3
unnamed: R804.2, R808.1, U803.4
unnamed: R805.1, U802.16
unnamed: R805.2, R806.1, U802.15
unnamed: R808.2, U803.1, U805.3
unnamed: R809.1, T801.12, U802.10
unnamed: R810.2, T801.10, U802.11
unnamed: R811.1, R814.2, U805.4
unnamed: R812.2, R813.1, U804.3
unnamed: R1004.2, U1004.23
unnamed: R1005.2, U1004.24
unnamed: R1012.2, U1003.8
unnamed: R1013.2, U1003.9
unnamed: U301.1, U303.3
unnamed: U302.1, U303.4
unnamed: U804.1, U806.1
unnamed: U805.1, U806.2
PM_MISO: J401.11, J1001.1, U1004.1
PM_MOSI: J401.12, J1001.4, U1004.2
PM_RESET: J401.14, J1001.5, R1006.2, U1004.31
PM_RJ45_LEDG: J401.8, R1004.1
PM_RJ45_LEDO: J401.9, R1005.1
PM_SCK: J401.13, J1001.3, U1004.12
PRECHARGE_CTL: Q901.1, R902.1, R904.1, U1003.16
PRECHARGE_LSD: J403.1, Q901.3
SCK_ISO: U802.4, U1004.28
SM_MISO: J401.4, J1002.1, U1003.1
SM_MOSI: J401.5, J1002.4, U1003.2
SM_RESET: J401.7, J1002.5, R1014.2, U1003.31
SM_RJ45_LEDG: J401.15, R1012.1
SM_RJ45_LEDO: J401.16, R1013.1
SM_SCK: J401.6, J1002.3, U1003.12
SS_BMS: Q504.3, R516.2, U1003.25
SS_HVD: Q502.3, R508.2, U1003.28
SS_HVD_CONN: Q501.3, R507.2, U1003.27
SS_IMD_LATCH: Q505.3, R517.2, U1003.24
SS_MPC: Q503.3, R509.2, U1003.26
SS_TSMS: Q506.3, R518.2, U1003.23
TS+: C701.2, F701.2, J404.1, J404.3, R601.2, U701.5, U701.6, U701.7, U701.8
TSAL_GREEN-: J402.9, J402.10, Q602.3
TSAL_RED-: J402.8, Q601.3
VOUT: J801.3, R802.1, R803.1, U804.4, U1004.18
VREF: J801.4, R804.1, U1004.17
nOCD: J801.5, R801.2, U1004.16

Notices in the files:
parts and their libraries:
Copyright 2016 Accelerated Designs. All rights reserved.
